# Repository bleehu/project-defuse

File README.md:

# project-defuse
A project to make an open-sourced hardware game in a similar vein to

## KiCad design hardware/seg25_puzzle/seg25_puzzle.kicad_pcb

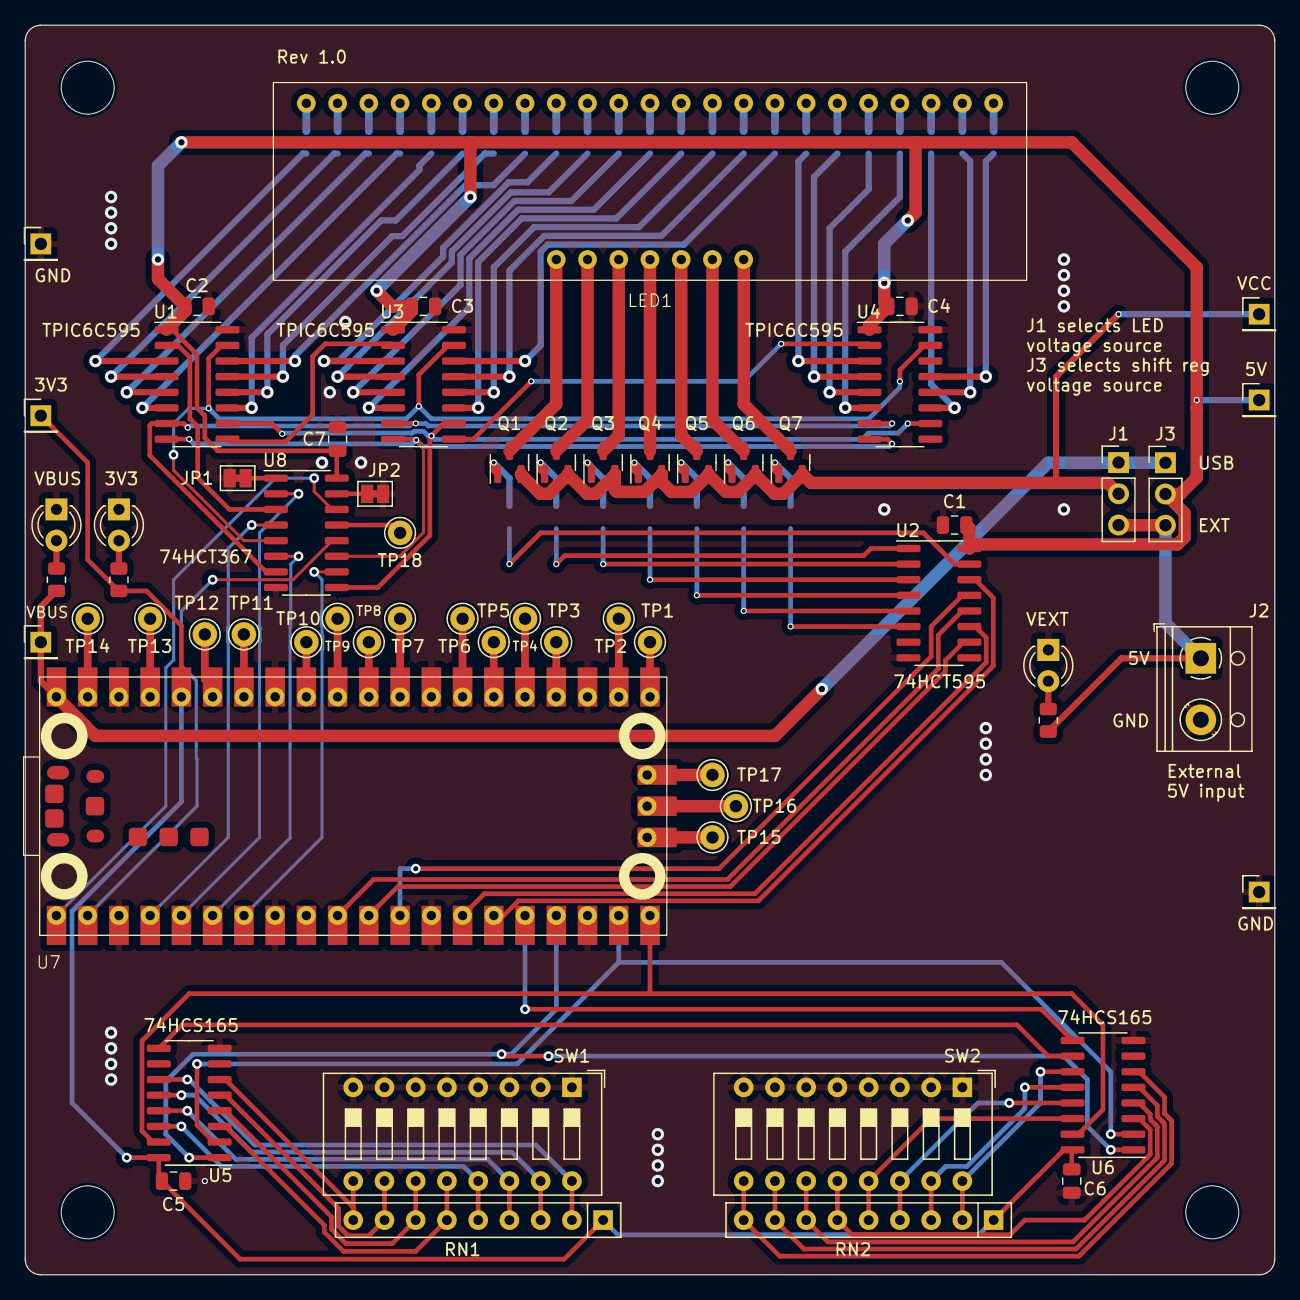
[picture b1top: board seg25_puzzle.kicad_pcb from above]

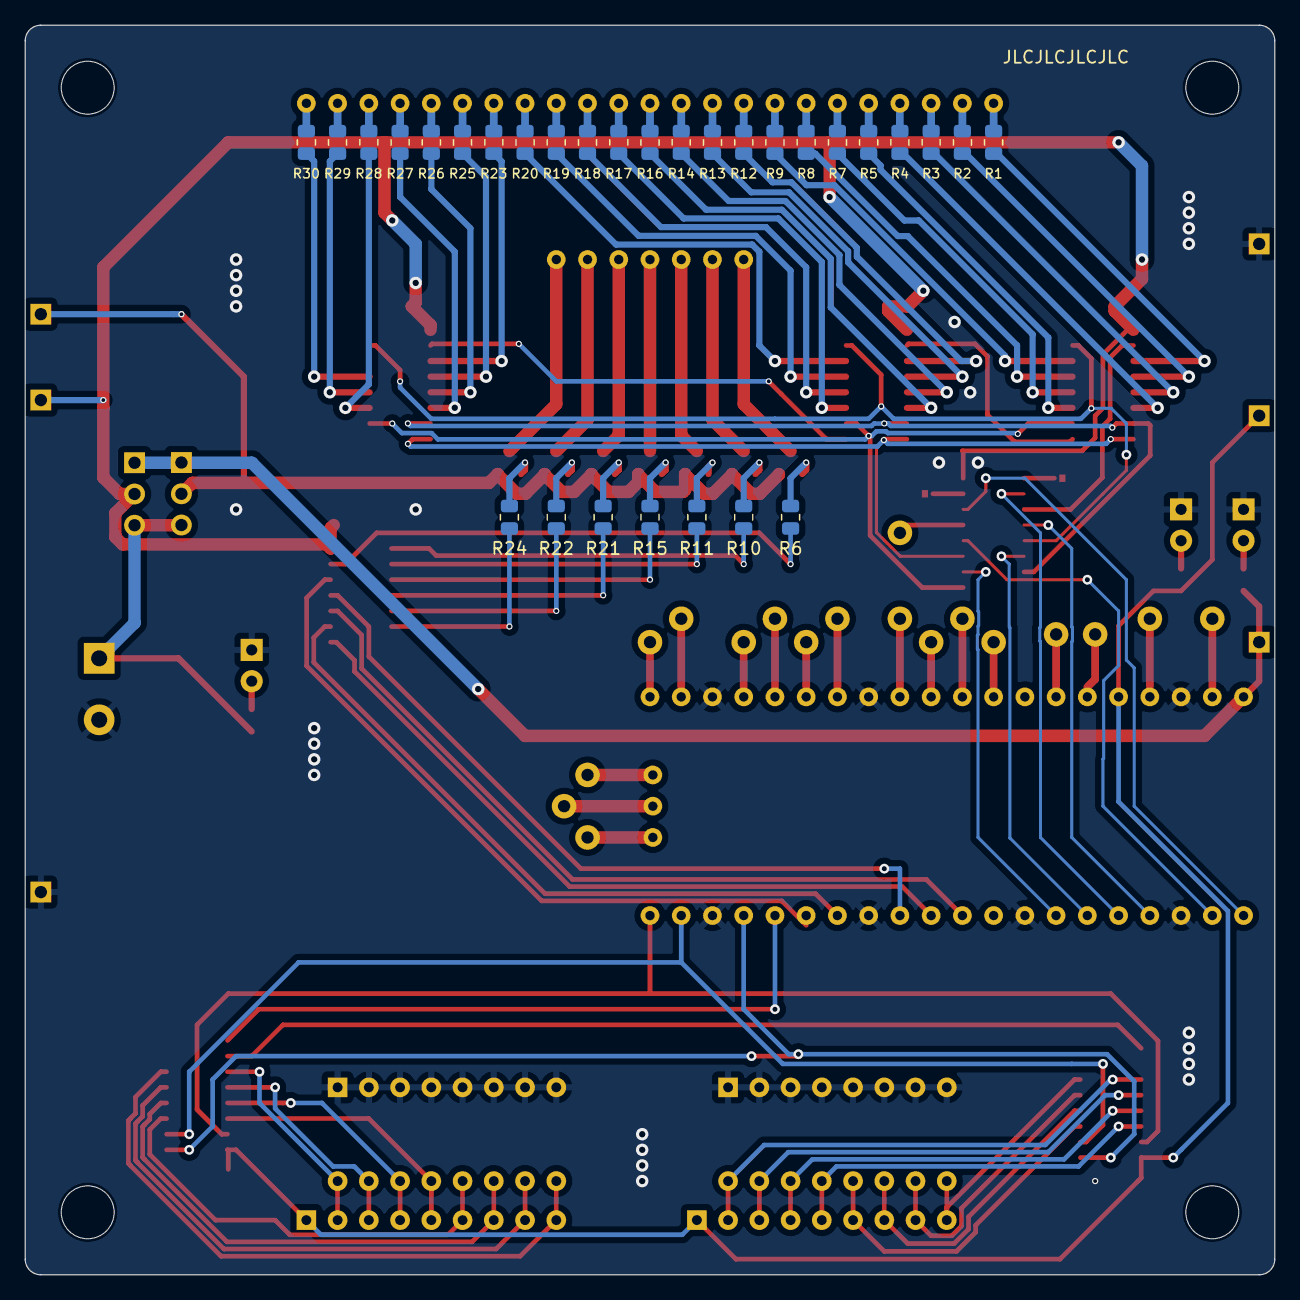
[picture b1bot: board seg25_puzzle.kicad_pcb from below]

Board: 2 copper layers, 101.6 x 101.6 mm, 96 parts (30 on the bottom side), 135 nets.

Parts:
C1, C2, C3, C4, C5, C6, C7: 100n; C_0805_2012Metric
D1, D2, D5: LED; LED_D3.0mm
H1, H2, H3, H4: MountingHole; MountingHole_4.3mm_M4
J1, J3: Conn_01x03_Pin; PinHeader_1x03_P2.54mm_Vertical
J2: Screw_Terminal_01x02; TerminalBlock_RND_205-00012_1x02_P5.00mm_Horizontal
JP1, JP2: Jump; SolderJumper-2_P1.3mm_Bridged_Pad1.0x1.5mm
LED1: DYSR00P401101
Q1, Q2, Q3, Q4, Q5, Q6, Q7: BC808; SOT-23
R1, R2, R3, R4, R5, R7, R8, R9, R12, R13, R14, R16, R17, R18, R19, R20, R23, R25, R26, R27, R28, R29, R30, R31, R32, R35: 1k; R_0805_2012Metric
R6, R10, R11, R15, R21, R22, R24: 10k; R_0805_2012Metric
RN1, RN2: 100k; R_Array_SIP9
SW1, SW2: SW_DIP_x08; SW_DIP_SPSTx08_Slide_9.78x22.5mm_W7.62mm_P2.54mm
TP1, TP2, TP3, TP4, TP5, TP6, TP7, TP8, TP9, TP10, TP11, TP12, TP13, TP14, TP15, TP16, TP17, TP18: TestPoint; Pin_D1.0mm_L10.0mm
TP19, TP20, TP21, TP22, TP23, TP24: TestPoint; PinHeader_1x01_P2.54mm_Vertical
U1, U3, U4: TPIC6C595; SOIC-16_3.9x9.9mm_P1.27mm
U2: 74HCT595; SOIC-16_3.9x9.9mm_P1.27mm
U5, U6: 74HCS165; SOIC-16_3.9x9.9mm_P1.27mm
U7: PiPico; PiPico_thru_and_surface
U8: 74HCT367; SOIC-16_3.9x9.9mm_P1.27mm

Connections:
165_CP: U5.2 (CP), U6.2 (CP), U7.19 (GP14)
165_MISO: U6.9 (Q7), U7.16 (GP12)
595_RCLK: U2.12 (RCLK), U7.10 (GP7)
595_SER: U2.14 (SER), U7.15 (GP11)
595_SRCLK: U2.11 (SRCLK), U7.14 (GP10)
+3V3: C5.1, C6.1, R32.2, RN1.1 (common), RN2.1 (common), TP22.1, U5.16 (VCC), U6.16 (VCC), U7.36 (3V3_OUT)
+5V: C1.1, C2.1, C3.1, C4.1, C7.1, J3.2, TP23.1, U1.1 (VCC), U2.16 (VCC), U3.1 (VCC), U4.1 (VCC), U8.16 (VCC)
/uC/SPARE_LEVEL_SHIFT: U7.1 (GP0), U8.14 (I6)
/uC/TPIC_CLR_3V3: U7.6 (GP4), U8.6 (I3)
/uC/TPIC_OE_3V3: U7.2 (GP1), U8.12 (I5)
/uC/TPIC_RCK_3V3: U7.7 (GP5), U8.10 (I4)
/uC/TPIC_SER_IN_3V3: U7.5 (GP3), U8.2 (I1)
/uC/TPIC_SRCK_3V3: U7.4 (GP2), U8.4 (I2)
GND: C1.2, C2.2, C3.2, C4.2, C5.2, C6.2, C7.2, D1.1 (K), D2.1 (K), D5.1 (K), J2.2, JP1.1 (A), JP2.1 (A), SW1.1, SW1.2, SW1.3, SW1.4, SW1.5, SW1.6, SW1.7, SW1.8, SW2.1, SW2.2, SW2.3, SW2.4, SW2.5, SW2.6, SW2.7, SW2.8, TP19.1, TP20.1, U1.16 (GND), U2.8 (GND), U3.16 (GND), U4.16 (GND), U5.8 (GND), U6.8 (GND), U7.3 (GND), U7.8 (GND), U7.13 (GND), U7.18 (GND), U7.23 (GND), U7.28 (GND), U7.33 (GND), U7.38 (GND), U8.8 (GND)
unnamed: D1.2 (A), R31.1
unnamed: D2.2 (A), R32.1
unnamed: D5.2 (A), R35.1
unnamed: J1.3, J2.1, J3.3, R35.2
unnamed: JP1.2 (B), U8.1 (OEa)
unnamed: JP2.2 (B), U8.15 (OEb)
unnamed: LED1.9 (COM1), Q1.3 (C)
unnamed: LED1.10 (COM2), Q2.3 (C)
unnamed: LED1.11 (COM3), Q3.3 (C)
unnamed: LED1.12 (COM4), Q4.3 (C)
unnamed: LED1.13 (COM5), Q5.3 (C)
unnamed: LED1.14 (COM6), Q6.3 (C)
unnamed: LED1.15 (COM7), Q7.3 (C)
unnamed: LED1.46 (a), R1.1
unnamed: LED1.45 (b), R2.1
unnamed: LED1.44 (c), R3.1
unnamed: LED1.43 (d), R4.1
unnamed: LED1.42 (e), R5.1
unnamed: LED1.41 (f), R7.1
unnamed: LED1.40 (g), R8.1
unnamed: LED1.39 (h), R9.1
unnamed: LED1.38 (i), R12.1
unnamed: LED1.37 (j), R13.1
unnamed: LED1.36 (k), R14.1
unnamed: LED1.35 (l), R16.1
unnamed: LED1.34 (m), R17.1
unnamed: LED1.33 (n), R18.1
unnamed: LED1.32 (o), R19.1
unnamed: LED1.31 (p), R20.1
unnamed: LED1.30 (r), R23.1
unnamed: LED1.29 (s), R25.1
unnamed: LED1.28 (t), R26.1
unnamed: LED1.27 (u), R27.1
unnamed: LED1.26 (v), R28.1
unnamed: LED1.25 (w), R29.1
unnamed: LED1.24 (x), R30.1
unnamed: Q1.1 (B), R6.2
unnamed: Q2.1 (B), R10.2
unnamed: Q3.1 (B), R11.2
unnamed: Q4.1 (B), R15.2
unnamed: Q5.1 (B), R21.2
unnamed: Q6.1 (B), R22.2
unnamed: Q7.1 (B), R24.2
unnamed: RN1.2 (R1), SW1.16, U5.11 (D0)
unnamed: RN1.3 (R2), SW1.15, U5.12 (D1)
unnamed: RN1.4 (R3), SW1.14, U5.13 (D2)
unnamed: RN1.5 (R4), SW1.13, U5.14 (D3)
unnamed: RN1.6 (R5), SW1.12, U5.3 (D4)
unnamed: RN1.7 (R6), SW1.11, U5.4 (D5)
unnamed: RN1.8 (R7), SW1.10, U5.5 (D6)
unnamed: RN1.9 (R8), SW1.9, U5.6 (D7)
unnamed: RN2.2 (R1), SW2.16, U6.11 (D0)
unnamed: RN2.3 (R2), SW2.15, U6.12 (D1)
unnamed: RN2.4 (R3), SW2.14, U6.13 (D2)
unnamed: RN2.5 (R4), SW2.13, U6.14 (D3)
unnamed: RN2.6 (R5), SW2.12, U6.3 (D4)
unnamed: RN2.7 (R6), SW2.11, U6.4 (D5)
unnamed: RN2.8 (R7), SW2.10, U6.5 (D6)
unnamed: RN2.9 (R8), SW2.9, U6.6 (D7)
unnamed: TP16.1, U7.D2 (GND)
unnamed: R1.2, U1.3 (DRAIN0)
unnamed: R2.2, U1.4 (DRAIN1)
unnamed: R3.2, U1.5 (DRAIN2)
unnamed: R4.2, U1.6 (DRAIN3)
unnamed: R5.2, U1.11 (DRAIN4)
unnamed: R7.2, U1.12 (DRAIN5)
unnamed: R8.2, U1.13 (DRAIN6)
unnamed: R9.2, U1.14 (DRAIN7)
unnamed: U1.9 (SER_OUT), U3.2 (SER_IN)
unnamed: R6.1, U2.15 (QA)
unnamed: R10.1, U2.1 (QB)
unnamed: R11.1, U2.2 (QC)
unnamed: R15.1, U2.3 (QD)
unnamed: R21.1, U2.4 (QE)
unnamed: R22.1, U2.5 (QF)
unnamed: R24.1, U2.6 (QG)
unnamed: R12.2, U3.3 (DRAIN0)
unnamed: R13.2, U3.4 (DRAIN1)
unnamed: R14.2, U3.5 (DRAIN2)
unnamed: R16.2, U3.6 (DRAIN3)
unnamed: R17.2, U3.11 (DRAIN4)
unnamed: R18.2, U3.12 (DRAIN5)
unnamed: R19.2, U3.13 (DRAIN6)
unnamed: R20.2, U3.14 (DRAIN7)
unnamed: U3.9 (SER_OUT), U4.2 (SER_IN)
unnamed: R23.2, U4.3 (DRAIN0)
unnamed: R25.2, U4.4 (DRAIN1)
unnamed: R26.2, U4.5 (DRAIN2)
unnamed: R27.2, U4.6 (DRAIN3)
unnamed: R28.2, U4.11 (DRAIN4)
unnamed: R29.2, U4.12 (DRAIN5)
unnamed: R30.2, U4.13 (DRAIN6)
unnamed: U5.9 (Q7), U6.10 (DS)
unnamed: TP13.1, U7.37 (3V3_EN)
unnamed: TP12.1, U7.35 (ADC_VREF)
unnamed: TP1.1, U7.21 (GP16)
unnamed: TP2.1, U7.22 (GP17)
unnamed: TP3.1, U7.24 (GP18)
unnamed: TP4.1, U7.25 (GP19)
unnamed: TP5.1, U7.26 (GP20)
unnamed: TP6.1, U7.27 (GP21)
unnamed: TP7.1, U7.29 (GP22)
unnamed: TP9.1, U7.31 (GP26)
unnamed: TP10.1, U7.32 (GP27)
unnamed: TP11.1, U7.34 (GP28)
unnamed: TP8.1, U7.30 (RUN)
unnamed: TP15.1, U7.D1 (SWCLK)
unnamed: TP17.1, U7.D3 (SWDIO)
unnamed: TP14.1, U7.39 (VSYS)
unnamed: TP18.1, U8.13 (O6b)
TPIC_OE: U1.8 (~G), U3.8 (~G), U4.8 (~G), U8.11 (O5b)
TPIC_RCK: U1.10 (RCLK), U3.10 (RCLK), U4.10 (RCLK), U8.9 (O4a)
TPIC_SER_IN: U1.2 (SER_IN), U8.3 (O1a)
TPIC_SRCK: U1.15 (SRCK), U3.15 (SRCK), U4.15 (SRCK), U8.5 (O2a)
VBUS: J1.1, J3.1, R31.2, TP21.1, U7.40 (VBUS)
VCC: J1.2, Q1.2 (E), Q2.2 (E), Q3.2 (E), Q4.2 (E), Q5.2 (E), Q6.2 (E), Q7.2 (E), TP24.1
~165_CE: U5.15 (~CE), U6.15 (~CE), U7.20 (GP15)
~165_PL: U5.1 (~PL), U6.1 (~PL), U7.17 (GP13)
~595_OE: U2.13 (~OE), U7.12 (GP9)
~595_SRCLR: U2.10 (~SRCLR), U7.11 (GP8)
~TPIC_CLR: U1.7 (~CLR), U3.7 (~CLR), U4.7 (~CLR), U8.7 (O3a)

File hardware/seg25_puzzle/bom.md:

| Qty | Part name | Link |
| --- | --------- | ---- |
|   3 | TPIC6C595 | https://www.mouser.com/ProductDetail/595-TPIC6C595DG4
|   1 | 74HCT595  | https://www.mouser.com/ProductDetail/621-74HCT595S16-13
|   2 | 8x DIP switch | https://www.mouser.com/ProductDetail/774-2068
|   2 | 8x resistor array 100k | https://www.mouser.com/ProductDetail/652-4609X-1LF-100K
|   1 | 74HCT367 | https://www.mouser.com/ProductDetail/771-74HCT367D-T
|   1 | Screw terminal 2-pin | https://www.mouser.com/ProductDetail/490-TB003-500-P02BE
|   1 | Raspberry Pi Pico | https://www.mouser.com/ProductDetail/713-102110545
|   7 | BC808 | https://www.mouser.com/ProductDetail/637-BC808-40
|   2 | 74HCS165 | https://www.mouser.com/ProductDetail/595-SN74HCS165DR
|   7 | 100nF 0805 | From stock
|   3 | LED 3mm | From stock
|   2 | Header 3-pin | From stock
|   1 | DYSR00P401101 | https://www.radio741.com/40495-6-digit-16-25-segment-display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
|  26 | 1k 0805 | From stock
|   7 | 10k 0805 | From stock

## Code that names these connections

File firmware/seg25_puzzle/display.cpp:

#include "display.h"

#include "pico/multicore.h"
#include "pico/mutex.h"


uint32_t char_to_segments(char16_t c)
{
    switch (c)
    {
    case  'A': return 0b11110011'00010001'00000000;
    case  'B': return 0b11111100'01010100'00000000;
    case  'C': return 0b11001111'00000000'00000000;
    case  'D': return 0b11111100'01000100'00000000;
    case  'E': return 0b11001111'00000001'00000000;
    case  'F': return 0b11000011'00000001'00000000;
    case  'G': return 0b11011111'00010000'00000000;
    case  'H': return 0b00110011'00010001'00000000;
    case  'I': return 0b11001100'01000100'00000000;
    case  'J': return 0b00111110'00000000'00000000;
    case  'K': return 0b00000011'00101001'00000000;
    case  'L': return 0b00001111'00000000'00000000;
    case  'M': return 0b00110011'10100000'00000000;
    case  'N': return 0b00110011'10001000'00000000;
    case  'O': return 0b11111111'00000000'00000000;
    case  'P': return 0b11100011'00010001'00000000;
    case  'Q': return 0b11111111'00001000'00000000;
    case  'R': return 0b11100011'00011001'00000000;
    case  'S': return 0b11011100'10010000'00000000;
    case  'T': return 0b11000000'01000100'00000000;
    case  'U': return 0b00111111'00000000'00000000;
    case  'V': return 0b00000011'00100010'00000000;
    case  'W': return 0b00110011'00001010'00000000;
    case  'X': return 0b00000000'10101010'00000000;
    case  'Y': return 0b00000000'10100100'00000000;
    case  'Z': return 0b11001100'00100010'00000000;

    case  '0': return 0b11111111'00100010'00000000;
    case  '1': return 0b00110000'00100000'00000000;
    case  '2': return 0b11101110'00010001'00000000;
    case  '3': return 0b11111100'00010000'00000000;
    case  '4': return 0b00110001'00010001'00000000;
    case  '5': return 0b11001101'00001001'00000000;
    case  '6': return 0b11011111'00010001'00000000;
    case  '7': return 0b11110000'00000000'00000000;
    case  '8': return 0b11111111'00010001'00000000;
    case  '9': return 0b11111101'00010001'00000000;

    case  '!': return 0b00000000'01000100'00000100;
    case  '@': return 0b11101111'01010000'00000000;
    case  '#': return 0b00111100'01010101'00000000;
    case  '$': return 0b11011101'01010101'00000000;
    case  '%': return 0b10011001'01110111'00000000;
    case  '*': return 0b00000000'11111111'00000000;
    case  '(': return 0b00000000'00101000'00000000;
    case  ')': return 0b00000000'10000010'00000000;
    case  '-': return 0b00000000'00010001'00000000;
    case  '=': return 0b00001100'00010001'00000000;
    case  '_': return 0b00001100'00000000'00000000;
    case  '+': return 0b00000000'01010101'00000000;
    case  '<': return 0b00000000'00100100'00000000;
    case  '>': return 0b00000000'10000010'00000000;
    case  '[': return 0b01001000'01000100'00000000;
    case  ']': return 0b10000100'01000100'00000000;

    case  '/': return 0b00000000'00100010'00000000;
    case  '|': return 0b00000000'01000100'00000000;
    case '\\': return 0b00000000'10001000'00000000;
    case  '?': return 0b11100000'00010100'00000100;

    case u'β': return 0b10000111'01000101'00000010;
    case u'Γ': return 0b11000011'00000000'00000000;
    case u'Σ': return 0b11001100'10000010'00000000;
    case u'δ': return 0b11011110'10010001'00000000;
    case u'ζ': return 0b11000110'00100001'00000100;
    case u'λ': return 0b00000000'10001010'00000000;
    case u'μ': return 0b00011110'00000000'00000010;
    case u'Ξ': return 0b11001100'00010001'00000000;
    case u'Π': return 0b11110011'00000000'00000000;
    case u'π': return 0b00000000'00011011'00000000;
    case u'σ': return 0b00000110'00010101'00000000;
    case u'Ψ': return 0b00100001'01010101'00000000;

    case u'א': return 0b00100010'10011001'00000000;
    default:   return 0b11111111'11111111'11111111;
    }
}


Display string_to_display(const char16_t* str)
{
    // Zero-init, so we can just stop when we reach the end of the string
    Display result {};
    for (int i = 0; i < 6; ++i)
    {
        if (str[i] == 0)
        {
            break;
        }
        else
        {
            result.digits[i] = char_to_segments(str[i]);
        }
    }
    return result;
}

// Same implementation as the char16_t* above.
// char will be implicitly cast to char16_t when calling char_to_segments().
Display string_to_display(const char* str)
{
    // Zero-init, so we can just stop when we reach the end of the string
    Display result {};
    for (int i = 0; i < 6; ++i)
    {
        if (str[i] == 0)
        {
            break;
        }
        else
        {
            result.digits[i] = char_to_segments(str[i]);
        }
    }
    return result;
}




const uint tpic_OE = 1;
const uint tpic_SRCK = 2;
const uint tpic_SER_IN = 3;
const uint tpic_CLR = 4;
const uint tpic_RCK = 5;

const uint digit_RCLK = 7;
const uint digit_SRCLR = 8;
const uint digit_OE = 9;
const uint digit_SRCLK = 10;
const uint digit_SER = 11;

void setup_display_gpio()
{
    gpio_init(tpic_OE);
    gpio_init(tpic_SRCK);
    gpio_init(tpic_SER_IN);
    gpio_init(tpic_CLR);
    gpio_init(tpic_RCK);
    gpio_init(digit_RCLK);
    gpio_init(digit_SRCLR);
    gpio_init(digit_OE);
    gpio_init(digit_SRCLK);
    gpio_init(digit_SER);

    gpio_set_dir(tpic_OE, GPIO_OUT);
    gpio_set_dir(tpic_SRCK, GPIO_OUT);
    gpio_set_dir(tpic_SER_IN, GPIO_OUT);
    gpio_set_dir(tpic_CLR, GPIO_OUT);
    gpio_set_dir(tpic_RCK, GPIO_OUT);
    gpio_set_dir(digit_RCLK, GPIO_OUT);
    gpio_set_dir(digit_SRCLR, GPIO_OUT);
    gpio_set_dir(digit_OE, GPIO_OUT);
    gpio_set_dir(digit_SRCLK, GPIO_OUT);
    gpio_set_dir(digit_SER, GPIO_OUT);

    // Disable output on both shift registers
    gpio_put(tpic_OE, 1);
    gpio_put(digit_OE, 1);

    // De-assert clear (active low) on both
    gpio_put(tpic_CLR, 1);
    gpio_put(digit_SRCLR, 1);
}

void write_to_display(uint8_t digitIndex, uint32_t segments)
{
    // Disable output on both shift registers
    gpio_put(tpic_OE, 1);
    gpio_put(digit_OE, 1);


    // Shift out the segments
    gpio_put(tpic_SRCK, 0);
    gpio_put(tpic_RCK, 0);
    for (uint8_t i = 0; i < 24; ++i)
    {
        gpio_put(tpic_SER_IN, (segments >> i) & 1);
        gpio_put(tpic_SRCK, 1);
        gpio_put(tpic_SRCK, 0);
    }
    // Transfer from shift register to output register
    gpio_put(tpic_RCK, 1);
    gpio_put(tpic_RCK, 0);


    // Only light one digit at a time.
    // This is inverted because we're using PNPs
    uint8_t digitWord = ~(1 << (7 - digitIndex));

    // Shift out the digit
    gpio_put(digit_SRCLK, 0);
    for (uint8_t i = 0; i < 8; ++i)
    {
        gpio_put(digit_SER, (digitWord >> i) & 1);
        gpio_put(digit_SRCLK, 1);
        gpio_put(digit_SRCLK, 0);
    }
    // Transfer from shift register to output register
    gpio_put(digit_RCLK, 1);
    gpio_put(digit_RCLK, 0);


    // Enable outputs
    gpio_put(tpic_OE, 0);
    gpio_put(digit_OE, 0);
}

// Data to display, and a mutex to make updates atomic
Display displayData;
mutex_t displayDataMutex;

void core1_display_loop()
{
    while (true)
    {
        mutex_enter_blocking(&displayDataMutex);
        Display localDisplayData = displayData;
        mutex_exit(&displayDataMutex);

        for (int i = 0; i < 7; ++i)
        {
            write_to_display(i, localDisplayData.digits[i]);
            sleep_ms(1);
        }
    }
}

void init_display()
{
    displayData = {};

    mutex_init(&displayDataMutex);

    setup_display_gpio();

    multicore_launch_core1(&core1_display_loop);
}

void update_display(Display display)
{
    mutex_enter_blocking(&displayDataMutex);
    displayData = display;
    mutex_exit(&displayDataMutex);
}

void update_display(const char16_t* str)
{
    update_display(string_to_display(str));
}

void update_display(const char* str)
{
    update_display(string_to_display(str));
}

void add_marks_to_digit(Display& display, int digit, uint16_t marks)
{
    if (digit < 0 || digit > 5) return;

    display.digits[digit] |= marks & 0xFF;

    display.digits[6] |= ((marks >> 8) & 3) << (22 - 2 * digit);
}

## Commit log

2024-02-07 Initial commit with 25-segment display / DIP switch puzzle board 1.0
2024-02-07 Add BOM and Interactive BOM
2024-02-17 Add a blink example project for the prototype board
2024-02-17 Write a hello world message to the display
2024-02-17 Add switch support
    Generate random characters except when all switches are off, then it displays "Hello!"
2024-02-17 Add mode to turn all segments on
2024-02-18 Add support for characters and strings
    Supports uppercase Latin letters, Arabic numerals, an assortment of symbols and Greek letters, and aleph.
2024-02-18 Move display code to a separate file, and use the second core to update display
2024-02-18 Move switch reading code to a separate file
2024-02-19 Add support for adding additional marks to characters
